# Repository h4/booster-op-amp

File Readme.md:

# Simple Clean Booster

OP-Amp guitar booster. Circuit based on [Deep Blue Delay bufer stage](https://sfxguitareffects.blogspot.com/2012/07/building-clean-boost-inspired-by-deep.html) but adopted to using more common electronic parts.

## Documentation

This project is created using [KiCAD](https://kicad-pcb.org/) v5.1.5. Gerber files are located in `fab` directory. Custom footprints may be found in `booster-op-amp.pretty` directory.

# Bill of Materials

| Designator | Package             | Quantity |
| ---------- | ------------------- | -------- |
| C1         | 47uF 16v            | 1        |
| C2         | 22nF                | 1        |
| C3         | 47pF                | 1        |
| C4         | 100pF               | 1        |
| R1,R2,R7   | 10K                 | 3        |
| R3         | 1M                  | 1        |
| R4         | 200K                | 1        |
| R5         | 300K                | 1        |
| R6         | 20K                 | 1        |
| R8         | 1K                  | 1        |
| R9         | 100K                | 1        |
| RV1        | 50KB (Linear)       | 1        |
| U1         | TL072, DIP8 Package | 1        |

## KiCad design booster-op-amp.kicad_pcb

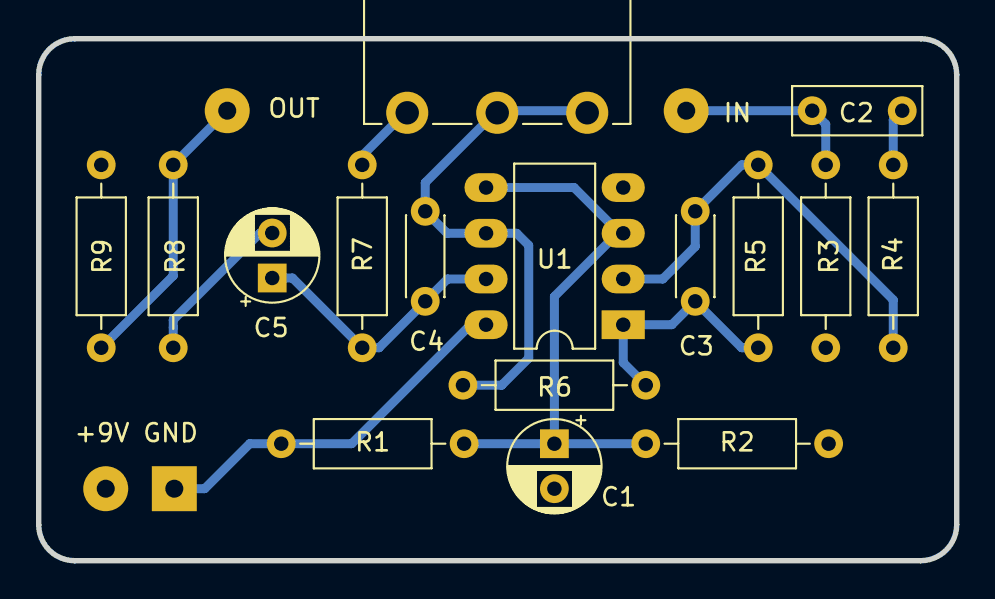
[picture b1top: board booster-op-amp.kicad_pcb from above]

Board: 2 copper layers, 51.0 x 29.0 mm, 19 parts (0 on the bottom side), 12 nets.

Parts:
C1: 47u; CP_Radial_D5.0mm_P2.50mm
C2: 22n; C_Rect_L7.0mm_W2.5mm_P5.00mm
C3: 47p; C_Disc_D4.3mm_W1.9mm_P5.00mm
C4: 100p; C_Disc_D4.3mm_W1.9mm_P5.00mm
C5: 1u; CP_Radial_D5.0mm_P2.50mm
J1: IN; SolderWirePad_1x01_Drill1mm
J2: OUT; SolderWirePad_1x01_Drill1mm
J3: PWR; SolderWirePad_1x02_P3.81mm_Drill1mm
R1, R2, R7: 10K; R_Axial_DIN0207_L6.3mm_D2.5mm_P10.16mm_Horizontal
R3: 1M; R_Axial_DIN0207_L6.3mm_D2.5mm_P10.16mm_Horizontal
R4: 200K; R_Axial_DIN0207_L6.3mm_D2.5mm_P10.16mm_Horizontal
R5: 300K; R_Axial_DIN0207_L6.3mm_D2.5mm_P10.16mm_Horizontal
R6: 20K; R_Axial_DIN0207_L6.3mm_D2.5mm_P10.16mm_Horizontal
R8: 1K; R_Axial_DIN0207_L6.3mm_D2.5mm_P10.16mm_Horizontal
R9: 100K; R_Axial_DIN0207_L6.3mm_D2.5mm_P10.16mm_Horizontal
RV1: 50KB; Potentiometer_Alpha_RV16AF_Single_Vertical_PCB_Mount
U1: TL072; DIP-8_W7.62mm_LongPads

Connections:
+9V: J3.1, R1.1, U1.8
/IN: C2.2, J1.1, R3.2
/OUT: J2.1, R8.1, R9.2
/VREF: C1.1, R1.2, R2.1, U1.3, U1.5
GND: C1.2, J3.2, R2.2, R3.1, R9.1, U1.4
unnamed: C2.1, R4.2
unnamed: C3.1, R5.1, R6.2, U1.1
unnamed: C3.2, R4.1, R5.2, U1.2
unnamed: C4.1, C5.1, R7.1, U1.7
unnamed: C4.2, R6.1, RV1.2, RV1.3, U1.6
unnamed: C5.2, R8.2
unnamed: R7.2, RV1.1

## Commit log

2020-08-09 Iinitial Commit
